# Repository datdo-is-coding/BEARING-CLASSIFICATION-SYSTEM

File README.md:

# 🏭 HỆ THỐNG KIỂM TRA & PHÂN LOẠI VÒNG BI TỰ ĐỘNG
## (AUTOMATED BEARING CLASSIFICATION SYSTEM)

Hệ thống tự động hóa công nghiệp kiểm tra và phân loại khuyết tật vòng bi kết hợp **Kiến trúc phân tán Edge - Cloud/Web**:
- **Trạm Điều Khiển Tại Chỗ (Edge Station - C# WinForms)**: Giao tiếp trực tiếp với phần cứng mạch điều khiển ESP32, thu nhận Camera DirectShow, chạy suy luận AI cục bộ 2 tầng (**YOLOv8 + ResNet-34 qua ONNX Runtime**) và điều khiển cánh tay Robot 4 bậc tự do (**4-DOF Arm**).
- **Hệ Thống Web Quản Lý & Giám Sát IoT (Central Web Dashboard - Python Flask)**: Kết nối với App C# qua **Mạng LAN nội bộ hoặc Internet (TCP/IP)**, cung cấp giao diện Web trực quan theo dõi thời gian thực, quản lý thống kê sản lượng OK/NG, lưu trữ lịch sử SQLite và điều khiển từ xa.
- **Phần Cứng & Cơ Điện Tử (Embedded & Mechatronics)**: Vi điều khiển **ESP32**, băng tải cấp phôi cảm biến quang NPN, mạch công suất cách ly và đầu gắp **nam châm điện (Electromagnet)**.

---

## 📑 Bảng Mục Lục
1. [Kiến Trúc Tổng Thể Hệ Thống](#-1-kiến-trúc-tổng-thể-hệ-thống)
2. [Quy Trình Hoạt Động (End-to-End Workflow)](#-2-quy-trình-hoạt-động-end-to-end-workflow)
3. [Chi Tiết Các Phân Hệ Công Nghệ](#-3-chi-tiết-các-phân-hệ-công-nghệ)
   - [3.1. Trạm điều khiển C# WinForms (Edge Control App)](#31-trạm-điều-khiển-c-winforms-edge-control-app)
   - [3.2. Web Quản Lý & Giám Sát IoT (Flask Dashboard Server)](#32-web-quản-lý--giám-sát-iot-flask-dashboard-server)
   - [3.3. Pipeline AI 2 tầng: YOLOv8n + ResNet-34 (ONNX Runtime)](#33-pipeline-ai-2-tầng-yolov8n--resnet-34-onnx-runtime)
   - [3.4. Vi điều khiển nhúng ESP32 & Động học Robot (Firmware)](#34-vi-điều-khiển-nhúng-esp32--động-học-robot-firmware)
   - [3.5. Phần cứng, Mạch PCB & Cơ khí (Hardware & Mechanics)](#35-phần-cứng-mạch-pcb--cơ-khí-hardware--mechanics)
4. [Giao Thức Truyền Thông & Kết Nối Đa Tầng](#-4-giao-thức-truyền-thông--kết-nối-đa-tầng)
   - [4.1. Giao tiếp LAN / TCP/IP (App C# $\leftrightarrow$ Web Quản lý)](#41-giao-tiếp-lan--tcpip-app-c--web-quản-lý)
   - [4.2. Giao tiếp Serial UART (App C# $\leftrightarrow$ Bo mạch ESP32)](#42-giao-tiếp-serial-uart-app-c--bo-mạch-esp32)
5. [Cấu Trúc Thư Mục Dự Án](#-5-cấu-trúc-thư-mục-dự-án)
6. [Hướng Dẫn Cài Đặt & Vận Hành](#-6-hướng-dẫn-cài-đặt--vận-hành)
7. [Kết Quả Đạt Được](#-7-kết-quả-đạt-được)

---

## 🏛️ 1. Kiến Trúc Tổng Thể Hệ Thống

Hệ thống được thiết kế theo mô hình phân tầng công nghiệp hiện đại (**Edge Controller $\leftrightarrow$ IoT Web Server**):

```
┌────────────────────────────────────────────────────────────────────────────────────────┐
│                   HỆ THỐNG GIÁM SÁT & QUẢN LÝ TRUNG TÂM (WEB IOT DASHBOARD)             │
│                                                                                        │
│   • Nền tảng: Python Flask / HTML5 / CSS3 / JavaScript / SQLite                        │
│   • Truy cập đa thiết bị: Trình duyệt PC, Tablet, Smartphone qua LAN / Internet        │
│   • Chức năng: Thống kê sản lượng Realtime, Giám sát Camera Snapshot, Lịch sử DB,       │
│                Điều khiển bắt đầu/dừng, Chế độ Mô phỏng / Thực tế                      │
└───────────────────────────────────────────▲────────────────────────────────────────────┘
                                            │
                                            │ MẠNG LAN / INTERNET (TCP/IP - HTTP REST API)
                                            │ • POST /api/detection (Kết quả AI, độ tin cậy)
                                            │ • POST /api/heartbeat (Trạng thái Online/Offline)
                                            │ • GET /api/status     (Trạng thái điều khiển)
                                            │ • GET /snapshot.jpg   (Hình ảnh camera trạm)
                                            ▼
┌────────────────────────────────────────────────────────────────────────────────────────┐
│                   TRẠM ĐIỀU KHIỂN & SUY LUẬN TẠI CHỖ (APP C# WINFORMS)                  │
│                                                                                        │
│   ┌────────────────────────────────────────┐  ┌─────────────────────────────────────┐  │
│   │        GIAO DIỆN WINFORMS (.NET 8)     │  │        ONNX RUNTIME AI PIPELINE     │  │
│   │  • Video Stream trực tiếp (OpenCV)     │  │  • Stage 1: yolo_bearing.onnx       │  │
│   │  • Mô phỏng Robot 3D (WPF/SharpDX)     │  │    (Định vị Bounding Box & Tâm)     │  │
│   │  • Quản lý cổng COM & cấu hình mạng    │  │  • Stage 2: resnet34_bearing.onnx   │  │
│   │  • Đồng bộ dữ liệu sang Web Dashboard  │  │    (Phân loại 4 lớp khuyết tật)     │  │
│   └────────────────────────────────────────┘  └─────────────────────────────────────┘  │
└───────────────────▲────────────────────────────────────────────▲───────────────────────┘
                    │                                            │
  (Camera Feed USB) │                                            │ Giao tiếp Serial UART
  DirectShow/OpenCV │                                            │ (Baud 9600/115200)
                    │                                            ▼
┌───────────────────┴───────┐                 ┌──────────────────────────────────────────┐
│  CAMERA QUAN SÁT TẠI TRẠM │                 │  BO MẠCH ĐIỀU KHIỂN TRUNG TÂM (ESP32)   │
│  • Độ phân giải cao       │                 │  • Thu nhận tín hiệu Cảm biến quang 24V  │
│  • Tiêu cự chuẩn buồng soi│                 │  • Giải thuật Động học nghịch (4-DOF IK) │
└───────────────────────────┘                 │  • Giao tiếp I2C điều khiển PCA9685      │
                                              │  • Đóng cắt MOSFET Băng tải & Nam châm   │
                                              └────────────────────┬─────────────────────┘
                                                                   │ (PWM 50Hz & Công suất)
                                                                   ▼
                                              ┌──────────────────────────────────────────┐
                                              │      CƠ CẤU CHẤP HÀNH NGOẠI VI           │
                                              │  • Động cơ Servo MG996R (Joint 1, 2, 3)  │
                                              │  • Micro Servo SG90 (Joint 4 Wrist)      │
                                              │  • Nam châm điện từ tính gắp phôi        │
                                              │  • Động cơ DC kéo Băng tải cấp phôi      │
                                              │  • Cảm biến quang phát hiện vị trí phôi  │
                                              └──────────────────────────────────────────┘
```

---

## 🔄 2. Quy Trình Hoạt Động (End-to-End Workflow)

```mermaid
flowchart TD
    A([Khởi động hệ thống]) --> B[App C# kết nối ESP32 qua Serial & Camera USB]
    B --> C[App C# kết nối Web Dashboard qua LAN/TCP-IP]
    C --> D[Web Dashboard phát lệnh BẮT ĐẦU CHU TRÌNH]
    D --> E[App C# kích hoạt Băng tải chạy cấp vòng bi]
    E --> F{Cảm biến quang phát hiện phôi?}
    F -- Chưa tới --> E
    F -- Đã phát hiện --> G[ESP32 báo ngắt -> App C# dừng Băng tải]
    G --> H[Camera chụp khung hình tĩnh trạm soi]
    H --> I[AI Stage 1: YOLOv8n phát hiện & crop vùng vòng bi ROI]
    I --> J[AI Stage 2: ResNet-34 phân loại 4 lớp khuyết tật]
    J --> K{Kết quả đánh giá?}
    K -- Normal --> L[Xác định: ĐẠT CHUẨN - OK]
    K -- Rusted / Damaged / Scratched --> M[Xác định: LỖI - NG]
    L --> N[App C# gửi HTTP POST /api/detection sang Web Dashboard]
    M --> N
    N --> O[Web cập nhật số lượng OK/NG & hiển thị nhật ký]
    L --> P[App C# tính toán tọa độ Cartesian chuyển lệnh UART sang ESP32]
    M --> P
    P --> Q[ESP32 giải IK -> Điều khiển Robot di chuyển đến tọa độ phôi]
    Q --> R[Bật Nam châm điện: Hút giữ vòng bi]
    R --> S[Robot nhấc phôi, quay thả vào khay tương ứng OK hoặc NG]
    S --> T[Ngắt Nam châm điện -> Robot trở về vị trí HOME]
    T --> U[ESP32 gửi tín hiệu hoàn thành chu trình về App C#]
    U --> V{Tiếp tục chu trình?}
    V -- Có --> E
    V -- Dừng --> W([Kết thúc vận hành])
```

---

## 🛠️ 3. Chi Tiết Các Phân Hệ Công Nghệ

### 3.1. Trạm Điều Khiển C# WinForms (Edge Control App)
*Thư mục mã nguồn: `software/DashBoardBearing/`*
- **Nền tảng**: `.NET 8.0 Windows Forms` kết hợp `WPF Interop` (`ElementHost`).
- **Giao tiếp phần cứng**:
  - Giao tiếp nối tiếp **Serial UART** (`System.IO.Ports`) đa luồng với ESP32: tự động kết nối lại khi mất tín hiệu, xử lý tập lệnh không đồng bộ không gây khóa giao diện.
  - Thu nhận hình ảnh trực tiếp qua `OpenCvSharp4` và `AForge.Video.DirectShow`.
- **Mô phỏng 3D thời gian thực**: Sử dụng `HelixToolkit.Wpf` và `SharpDX` mô phỏng trực quan chuyển động 4 khớp của Robot theo phản hồi thực tế từ ESP32.
- **Client LAN TCP/IP**:
  - Đóng vai trò Client gửi dữ liệu giám sát (`HttpClient`) lên Web Dashboard.
  - Cung cấp HTTP Endpoint nội bộ để Web Dashboard có thể đọc ảnh snapshot camera hiện tại.

### 3.2. Web Quản Lý & Giám Sát IoT (Flask Dashboard Server)
*Thư mục mã nguồn: `software/RobotBearingDashboard/`*
- **Nền tảng**: Python 3.10+, Flask, SQLite (`bearing.db`), HTML5/CSS3/JavaScript.
- **Tính năng trọng tâm**:
  - **Giám sát trực quan**: Hiển thị ảnh chụp trực tiếp từ trạm kiểm tra, nhãn phân loại, độ tin cậy và trạng thái chu trình.
  - **Thống kê sản lượng thời gian thực**: Biểu đồ trực quan và bộ đếm tổng sản phẩm, số lượng Đạt chuẩn (OK), các nhóm lỗi (Rỉ sét, Hư nắp, Khuyết tật bề mặt).
  - **Trạng thái phần cứng (Heartbeat)**: Giám sát tình trạng Online/Offline của module AI, Camera và mạch ESP32.
  - **Điều khiển từ xa**: Cho phép người quản trị ra lệnh Bắt đầu (`start`), Tạm dừng (`stop`), Đặt lại dữ liệu (`reset`) và chọn chế độ `real` (thực tế) hoặc `simulation` (mô phỏng).
  - **Lưu trữ & Xuất dữ liệu**: Tự động lưu nhật ký chi tiết vào SQLite và hỗ trợ trích xuất lịch sử phân loại.

### 3.3. Pipeline AI 2 Tầng: YOLOv8n + ResNet-34 (ONNX Runtime)
Hệ thống sử dụng cơ chế xử lý phân tầng nhằm tối ưu đồng thời tốc độ và độ chính xác:

| Tiêu chí | Giai đoạn 1 (Stage 1 - Detection) | Giai đoạn 2 (Stage 2 - Classification) |
| :--- | :--- | :--- |
| **Mô hình** | **YOLOv8n (Nano)** | **ResNet-34 (Deep Residual Net)** |
| **Vai trò** | Định vị Bounding Box & tọa độ tâm phôi $(X_c, Y_c)$ | Phân tích cấu trúc vi khuyết tật bề mặt |
| **Kích thước đầu vào** | $640 \times 640 \times 3$ | $224 \times 224 \times 3$ (Vùng ROI cắt từ BBox) |
| **Số lượng nhãn** | 1 lớp: `bearing` | 4 lớp: `normal`, `damaged_shield`, `rusted`, `surface_damage` |
| **Độ chính xác** | **Precision**: 98.9% \| **mAP@50**: **99.46%** | **Độ chính xác tổng**: **97.45%** \| **Macro F1**: **97.18%** |
| **Thời gian thực thi** | ~15 – 25 ms | ~8 – 15 ms |
| **Triển khai tại App C#** | `Microsoft.ML.OnnxRuntime` (`yolo_bearing.onnx`) | `Microsoft.ML.OnnxRuntime` (`resnet34_bearing.onnx`) |

#### Chi tiết độ chính xác phân loại 4 lớp (Tập Test độc lập 235 mẫu):
- `normal` (Đạt chuẩn $\rightarrow$ **OK**): Precision **97.7%**, Recall **91.3%**, F1 **94.4%**.
- `damaged_shield` (Hư nắp chắn bụi $\rightarrow$ **NG**): Precision **97.7%**, Recall **100.0%**, F1 **98.8%**.
- `rusted` (Gỉ sét oxy hóa $\rightarrow$ **NG**): Precision **97.3%**, Recall **99.1%**, F1 **98.2%**.
- `surface_damage` (Trầy xước/khuyết tật mặt lăn $\rightarrow$ **NG**): Precision **97.3%**, Recall **97.3%**, F1 **97.3%**.

### 3.4. Vi Điều Khiển Nhúng ESP32 & Động Học Robot (Firmware)
*Thư mục mã nguồn: `firmware/`*
- **Vi điều khiển**: ESP32-WROOM-32D (2 nhân Xtensa 240MHz).
- **Môi trường phát triển**: PlatformIO Core / C++ Framework Arduino.
- **Động học nghịch (Inverse Kinematics - IK)**:
  - Giải phương trình động học giải tích xác định góc 4 khớp $\theta_1, \theta_2, \theta_3, \theta_4$ từ tọa độ đích $(X, Y, Z)$ gửi từ App C#.
  - Kiểm tra điều kiện biên không gian làm việc (`OUT OF WORKSPACE`) và tránh điểm kỳ dị (`SINGULARITY`).
- **Máy trạng thái điều khiển (FSM)**: `IDLE`, `WAIT_SENSOR`, `MOVE_PICK`, `MAG_ON`, `MOVE_PLACE`, `MAG_OFF`, `HOME`, `ERROR`.
- **Giao tiếp phần cứng ngoại vi**:
  - Giao tiếp I2C Master tới IC tạo xung PWM PCA9685 (tần số 50Hz, phân giải 12-bit).
  - Đọc tín hiệu ngắt từ cảm biến quang qua bộ cách ly quang Opto PC817.
  - Điều khiển tầng kích MOSFET đóng ngắt động cơ băng tải và cuộn hút nam châm điện.

### 3.5. Phần Cứng, Mạch PCB & Cơ Khí (Hardware & Mechanics)
*Thư mục thiết kế: `hardware/`*
- **Cơ cấu tay máy 4-DOF**:
  - Thiết kế 3D bằng SolidWorks (`SLDASM`, `STEP`).
  - Khớp 1 (Đế), Khớp 2 (Vai), Khớp 3 (Khuỷu): Sử dụng Servo kim loại lực kéo cao **MG996R**.
  - Khớp 4 (Cổ tay xoay đầu gắp): Sử dụng Micro Servo **SG90**.
  - Đầu gắp: Sử dụng **Nam châm điện (Electromagnet)** hút giữ bề mặt vòng bi chắc chắn, tích hợp mạch dập xung ngược Flyback Diode.
- **Mạch điện tử điều khiển (PCB Hardware)**:
  - Thiết kế hoàn chỉnh trên **KiCad EDA** (`robot4dof.kicad_sch`, `robot4dof.kicad_pcb`).
  - Khối nguồn hạ áp cách ly: XL4015 (5A) cấp riêng cho hệ thống Servo, XL1509 và AMS1117 cấp cho mạch logic ESP32 nhằm triệt tiêu nhiễu sụt áp khi khởi động động cơ.
- **Băng tải & Cảm biến**:
  - Băng tải đai cao su nguồn 24V tốc độ ổn định.
  - Cảm biến thu phát quang học NPN 24V định vị phôi dừng chính xác tại buồng chụp.

---

## 📡 4. Giao Thức Truyền Thông & Kết Nối Đa Tầng

```
┌────────────────────┐            Mạng LAN / TCP-IP (HTTP REST)            ┌──────────────────────┐
│  Web Quản Lý IoT   │ ◄─────────────────────────────────────────────────► │    App C# WinForms   │
│  (Flask Dashboard) │   POST /api/detection, POST /api/heartbeat,...      │    (Edge Control)    │
└────────────────────┘                                                     └──────────┬───────────┘
                                                                                      │
                                                                   Cáp Serial (UART)  │ Cổng COM Nối Tiếp
                                                                   Baud 9600 / 115200 │ 8-N-1
                                                                                      ▼
                                                                           ┌──────────────────────┐
                                                                           │  Bo Mạch Điều Khiển  │
                                                                           │       (ESP32)        │
                                                                           └──────────────────────┘
```

### 4.1. Giao Tiếp LAN / TCP/IP (App C# $\leftrightarrow$ Web Quản Lý)

Kết nối thông qua giao thức HTTP REST API qua mạng LAN nội bộ (hoặc Internet TCP/IP):

| Endpoint | Phương thức | Bên gửi | Dữ liệu truyền (Payload JSON) | Chức năng |
| :--- | :---: | :---: | :--- | :--- |
| `/api/detection` | `POST` | App C# $\rightarrow$ Web | `{"category": "OK", "confidence": 0.975, "source": "ai", "cycle_id": 102}` | Gửi kết quả phân loại vòng bi |
| `/api/heartbeat` | `POST` | App C# $\rightarrow$ Web | `{"ai_online": true, "camera_online": true, "esp_online": true}` | Cập nhật trạng thái phần cứng |
| `/api/status` | `GET` | Web $\leftrightarrow$ App C# | Trả về JSON trạng thái hệ thống, chế độ chạy và số lượng | Đồng bộ trạng thái giao diện |
| `/api/control` | `POST` | Web $\rightarrow$ App C# | `{"action": "start"}` (hoặc `"stop"`, `"reset"`, `"real"`, `"demo"`) | Gửi lệnh điều khiển từ xa |
| `/snapshot.jpg` | `GET` | Web $\rightarrow$ App C# | Trả về luồng ảnh JPEG khung hình hiện tại của camera | Hiển thị hình ảnh trạm soi trên Web |

### 4.2. Giao Tiếp Serial UART (App C# $\leftrightarrow$ Bo Mạch ESP32)
- **Thông số truyền**: Baudrate: `9600 bps` (hoặc `115200 bps`), Data Bits: `8`, Parity: `None`, Stop Bits: `1`, Ký tự ngắt dòng: `\n`.

#### Bảng Lệnh Từ App C# $\rightarrow$ ESP32:
| Cú pháp lệnh | Ý nghĩa | Mô tả |
| :--- | :--- | :--- |
| `START` | Bắt đầu chu trình nạp lệnh | Khởi động hàng đợi chuyển động |
| `MOV <x> <y> <z>` | Di chuyển đầu gắp đến tọa độ | Tọa độ điểm gắp hoặc điểm thả phôi (mm) |
| `MAG <1\|0>` | Đóng/Ngắt nam châm điện | `MAG 1`: Hút giữ phôi \| `MAG 0`: Thả phôi |
| `HOME` | Về vị trí chờ an toàn | Đưa 4 khớp về góc an toàn mặc định |
| `CONV <1\|0>` | Đóng/Ngắt băng tải | Điều khiển động cơ băng tải chạy/dừng |
| `STOP` | Dừng khẩn cấp | Dừng toàn bộ chuyển động ngay lập tức |

#### Bản Tin Phản Hồi Từ ESP32 $\rightarrow$ App C#:
| Bản tin phản hồi | Ý nghĩa |
| :--- | :--- |
| `SENSOR_TRIGGERED` | Tín hiệu cảm biến quang ngắt báo phôi đã đến trạm dừng |
| `A <J1> <J2> <J3> <J4>` | Góc quay hiện tại của 4 khớp servo (chu kỳ 50ms để render 3D) |
| `CYCLE_DONE <id>` | Báo hoàn thành chu trình gắp thả thành công |
| `IK ERROR: OUT OF WORKSPACE` | Cảnh báo tọa độ phôi nằm ngoài bán kính vươn tới của robot |

---

## 📂 5. Cấu Trúc Thư Mục Dự Án

```
BEARING-CLASSIFICATION-SYSTEM/
│
├── firmware/                              # Firmware nhúng điều khiển ESP32
│   ├── platformio.ini                     # Cấu hình PlatformIO & thư viện phụ thuộc
│   ├── include/                           # Thư viện header C++ (.hpp)
│   │   ├── CLI.hpp                        # Bộ thông dịch lệnh Serial UART
│   │   ├── control.hpp                    # Cấu hình I2C PCA9685 & xung servo
│   │   └── kinematics.hpp                 # Giải thuật Động học nghịch (IK 4-DOF)
│   └── src/                               # Mã nguồn C++ triển khai
│       ├── main.cpp                       # Điểm khởi chạy, hàm setup() & loop()
│       ├── CLI.cpp                        # Xử lý chuỗi lệnh nhận từ App C#
│       ├── control.cpp                    # Điều khiển PWM, MOSFET băng tải & nam châm
│       └── kinematics.cpp                 # Thuật toán tính góc các khớp
│
├── hardware/                              # Thiết kế cơ khí CAD và mạch điện tử PCB
│   ├── cad/                               # File mô hình 3D SolidWorks (.SLDASM, .STEP)
│   │   ├── Assem1.SLDASM                  # Lắp ráp tổng thể cánh tay Robot 4-DOF
│   │   ├── base.SLDPRT                    # Chi tiết bệ đỡ xoay
│   │   ├── arm bar.SLDPRT                 # Cụm cánh tay chịu lực
│   │   ├── magnet.SLDPRT                  # Gá giữ nam châm điện
│   │   └── mg996R_v2.step                 # Mô hình 3D chuẩn servo MG996R
│   └── pcb/                               # Thiết kế bo mạch KiCad EDA
│       ├── robot4dof.kicad_sch            # Sơ đồ nguyên lý mạch điều khiển
│       ├── robot4dof.kicad_pcb            # Bản vẽ layout bo mạch in
│       └── robot4dof_gerber/              # Tệp Gerber phục vụ gia công sản xuất
│
├── software/                              # Toàn bộ phần mềm hệ thống máy tính
│   │
│   ├── DashBoardBearing/                  # [EDGE] Ứng dụng điều khiển trung tâm C# WinForms
│   │   ├── DashBoardBearing.sln           # Visual Studio Solution (.NET 8.0)
│   │   ├── DashBoardBearing.csproj        # Cấu hình dependencies & NuGet Packages
│   │   ├── CameraManager.cs               # Bắt hình camera, OpenCV & gọi ONNX Runtime
│   │   ├── SerialManager.cs               # Giao tiếp nối tiếp COM/UART với ESP32
│   │   ├── RoundedPanel.cs                # Component giao diện phẳng hiện đại
│   │   ├── FormHome.cs                    # Màn hình camera live, nhận diện & gửi dữ liệu Web
│   │   ├── FormRobot.cs                   # Màn hình tích hợp mô phỏng Robot 3D (WPF/SharpDX)
│   │   ├── FormSetting.cs                 # Cấu hình cổng COM, Camera và IP Web Dashboard
│   │   ├── FormLog.cs                     # Ghi nhật ký vận hành tại chỗ
│   │   └── Model/                         # Trọng số mô hình AI xuất chuẩn ONNX
│   │       ├── yolo_bearing.onnx          # Model Stage 1: Phát hiện BBox vòng bi
│   │       └── resnet34_bearing.onnx      # Model Stage 2: Phân loại 4 lớp khuyết tật
│   │
│   └── RobotBearingDashboard/             # [WEB IOT] Ứng dụng Web Quản Lý & Giám Sát
│       └── RobotBearingDashboard/
│           ├── app.py                     # Máy chủ backend Python Flask & REST API
│           ├── requirements.txt           # Thư viện Flask, requests
│           ├── bearing.db                 # Cơ sở dữ liệu SQLite lưu trữ lịch sử
│           ├── templates/
│           │   └── index.html             # Giao diện Web Dashboard thời gian thực
│           ├── static/                    # CSS, JS, hình ảnh giao diện Web
│           ├── send_ai_example.py         # Script Python mẫu gửi dữ liệu test API
│           └── README.md                  # Hướng dẫn chi tiết phân hệ Web Dashboard
│
├── training/                              # Mã nguồn huấn luyện & nghiên cứu AI (PyTorch)
│   ├── configs/config.yaml                # Siêu tham số huấn luyện
│   ├── models/class_mapping.json          # Bảng ánh xạ ID nhãn sang tên lỗi
│   ├── weights/                           # Checkpoint trọng số tối ưu (.pt, .pth)
│   ├── tools/                             # Tool cắt ROI, gán nhãn, tiền xử lý dữ liệu
│   ├── training/                          # Script huấn luyện YOLOv8 & Fine-tune ResNet-34
│   ├── main.py                            # Script chạy thực nghiệm độc lập trên Python
│   └── requirements.txt                   # Thư viện Python (torch, torchvision, ultralytics)
│
├── NCKH_REQUIREMENT.md                    # Bảng theo dõi các nội dung hoàn thiện báo cáo NCKH
└── README.md                              # Tài liệu hướng dẫn tổng thể dự án
```

---

## 🚀 6. Hướng Dẫn Cài Đặt & Vận Hành

### 6.1. Chuẩn Bị Môi Trường
1. **Phần cứng**: Máy tính chạy Windows 10/11, bo mạch ESP32, bộ đổi nguồn 24V (băng tải) và 5V-6V (servo), cáp nối USB-UART, camera trạm soi.
2. **Phần mềm phát triển**:
   - Visual Studio 2022 (cài gói **.NET Desktop Development**).
   - .NET 8.0 SDK.
   - Python 3.10 trở lên.
   - VS Code có cài extension **PlatformIO IDE**.

---

### 6.2. Nạp Firmware Cho Bo Mạch ESP32
1. Mở thư mục `firmware/` bằng VS Code.
2. Cắm cáp USB nối ESP32 vào máy tính.
3. Nhấn nút **PlatformIO: Upload** trên thanh trạng thái để biên dịch và nạp firmware.

---

### 6.3. Khởi Chạy Web Quản Lý (Flask Web Dashboard)
1. Mở terminal (PowerShell) và chuyển vào thư mục Web Dashboard:
   ```powershell
   cd software/RobotBearingDashboard/RobotBearingDashboard
   ```
2. Tạo môi trường ảo và cài đặt thư viện:
   ```powershell
   py -m venv .venv
   .\.venv\Scripts\Activate.ps1
   pip install -r requirements.txt
   ```
3. Khởi chạy Web Server:
   ```powershell
   python app.py
   ```
4. Truy cập giao diện trên trình duyệt web:
   ```
   http://127.0.0.1:5000
   ```
   *(Hoặc truy cập qua địa chỉ IP mạng LAN của máy chủ: `http://192.168.x.x:5000`)*.

---

### 6.4. Khởi Chạy Ứng Dụng C# WinForms (Edge Control Station)
1. Mở `software/DashBoardBearing/DashBoardBearing.sln` bằng Visual Studio 2022.
2. Đảm bảo cấu hình đường dẫn IP Web Dashboard trong phần cấu hình mạng (mặc định: `http://127.0.0.1:5000` hoặc IP LAN của máy chủ).
3. Kiểm tra các mô hình AI ONNX đã nằm đúng trong thư mục `software/DashBoardBearing/Model/`:
   - `yolo_bearing.onnx`
   - `resnet34_bearing.onnx`
4. Chọn cấu hình **Release \| x64** và nhấn **Start (F5)** để khởi chạy ứng dụng.

---

### 6.5. Vận Hành Đồng Bộ Toàn Hệ Thống
1. **Trên App C# WinForms**:
   - Vào tab **Setting**: Chọn cổng COM của ESP32 (ví dụ: `COM3`, baudrate `9600`), nhấn **Connect Serial**.
   - Chọn Camera soi phôi trong danh sách và nhấn **Start Camera**.
   - Bật kết nối đồng bộ dữ liệu tới **Web Dashboard**.
2. **Trên Web Dashboard**:
   - Kiểm tra nhịp tim phần cứng: biểu tượng **AI Online**, **Camera Online**, **ESP Online** chuyển sang màu xanh.
   - Chọn chế độ **Thực tế (Real Mode)** và nhấn **Bắt đầu (Start)**.
3. **Chu trình tự động**:
   - Băng tải chạy cấp vòng bi vào buồng soi.
   - Khi cảm biến quang ngắt, băng tải dừng lại.
   - Camera chụp ảnh, App C# suy luận AI 2 tầng (YOLOv8 + ResNet-34).
   - App C# tự động gửi bản tin phân loại qua mạng LAN sang Web Dashboard để ghi log và thống kê.
   - App C# truyền lệnh gắp tới ESP32; Robot gắp thả vòng bi vào đúng khay phân loại (Khay OK hoặc Khay NG).
   - Sau khi hoàn thành, robot trở về vị trí Home và băng tải tiếp tục chạy cấp sản phẩm mới.

---

## 🏆 7. Kết Quả Đạt Được

- ✅ **Kiến trúc hệ thống phân tán hoàn chỉnh**: Kết hợp linh hoạt giữa khả năng điều khiển cứng thời gian thực của C# WinForms và khả năng giám sát từ xa đa nền tảng qua mạng LAN của Web IoT Flask.
- ✅ **Độ tin cậy nhận diện cao**: Mô hình AI 2 tầng đạt độ chính xác **97.45%**, phân loại chuẩn xác 4 trạng thái vòng bi công nghiệp.
- ✅ **Vận hành an toàn & đồng bộ**: Cơ chế khóa liên động giữa cảm biến quang, băng tải và máy trạng thái robot giúp loại bỏ nguy cơ va chạm cơ khí và lỗi kẹt phôi.
- ✅ **Khả năng mở rộng công nghiệp**: Dễ dàng tích hợp thêm các trạm kiểm tra mới vào cùng một Web Dashboard quản lý thông qua giao thức mạng TCP/IP tiêu chuẩn.

---
*Dự án thuộc Đề tài Nghiên cứu Khoa học Sinh viên - Khoa Tự động hoá, Trí tuệ nhân tạo và Hệ thống thông minh, Trường Đại học Điện lực.*

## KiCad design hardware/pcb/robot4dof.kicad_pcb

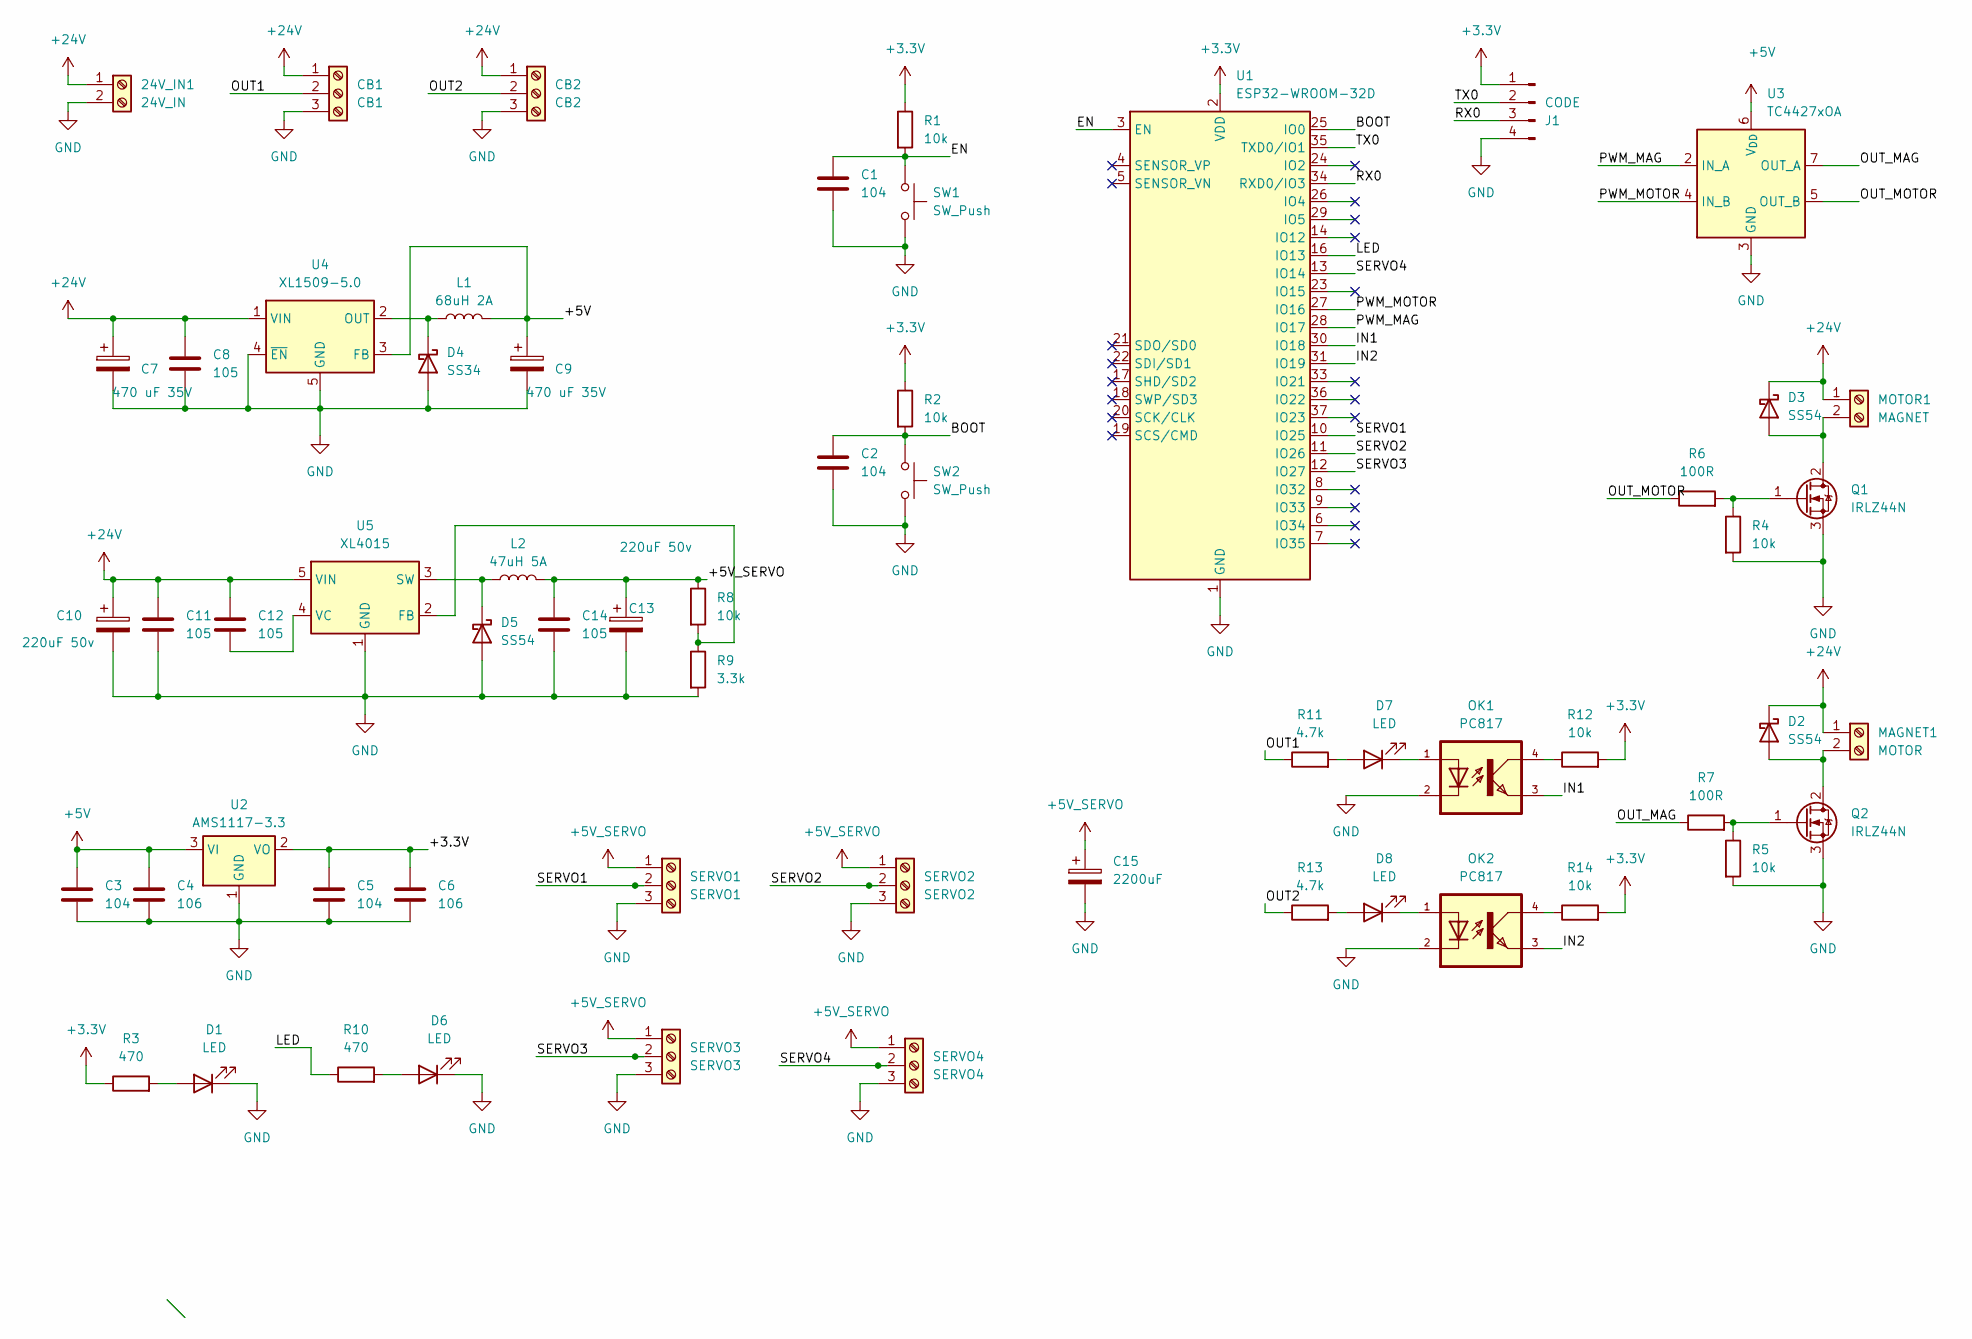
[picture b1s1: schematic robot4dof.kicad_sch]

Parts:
24V_IN1: 24V_IN; TerminalBlock_TE_282834-2_1x02_P2.54mm_Horizontal
C1, C2, C3, C5: 104; C_0805_2012Metric_Pad1.18x1.45mm_HandSolder
C4, C6: 106; C_0805_2012Metric_Pad1.18x1.45mm_HandSolder
C7, C9: 470 uF 35V; CP_Elec_8x10.5
C8, C11, C12, C14: 105; C_0805_2012Metric_Pad1.18x1.45mm_HandSolder
C10, C13: 220uF 50v; CP_Elec_8x10.5
C15: 2200uF; C_Radial_D10.0mm_H20.0mm_P5.00mm
CB1: CB1; TerminalBlock_TE_282834-3_1x03_P2.54mm_Horizontal
CB2: CB2; TerminalBlock_TE_282834-3_1x03_P2.54mm_Horizontal
D1, D6, D7, D8: LED; LED_0805_2012Metric_Pad1.15x1.40mm_HandSolder
D2, D3, D5: SS54; D_SMA_Handsoldering
D4: SS34; D_SMA_Handsoldering
J1: CODE; PinHeader_1x04_P2.54mm_Vertical
L1: 68uH 2A; L_7.3x7.3_H3.5
L2: 47uH 5A; L_Toroid_Vertical_L21.6mm_W9.1mm_P8.40mm_Bourns_5700
MAGNET1: MOTOR; TerminalBlock_TE_282834-2_1x02_P2.54mm_Horizontal
MOTOR1: MAGNET; TerminalBlock_TE_282834-2_1x02_P2.54mm_Horizontal
OK1, OK2: PC817; DIL04; MPN PC817X4J000F
Q1, Q2: IRLZ44N; TO-220-3_Vertical
R1, R2, R4, R5, R8, R12, R14: 10k; R_0805_2012Metric_Pad1.20x1.40mm_HandSolder
R3, R10: 470; R_0805_2012Metric_Pad1.20x1.40mm_HandSolder
R6, R7: 100R; R_0805_2012Metric_Pad1.20x1.40mm_HandSolder
R9: 3.3k; R_0805_2012Metric_Pad1.20x1.40mm_HandSolder
R11, R13: 4.7k; R_0805_2012Metric_Pad1.20x1.40mm_HandSolder
SERVO1: SERVO1; TerminalBlock_TE_282834-3_1x03_P2.54mm_Horizontal
SERVO2: SERVO2; TerminalBlock_TE_282834-3_1x03_P2.54mm_Horizontal
SERVO3: SERVO3; TerminalBlock_TE_282834-3_1x03_P2.54mm_Horizontal
SERVO4: SERVO4; TerminalBlock_TE_282834-3_1x03_P2.54mm_Horizontal
SW1, SW2: SW_Push; SW_Tactile_SPST_NO_Straight_CK_PTS636Sx25SMTRLFS
U1: ESP32-WROOM-32D
U2: AMS1117-3.3; SOT-223-3_TabPin2
U3: TC4427xOA; SOIC-8_3.9x4.9mm_P1.27mm
U4: XL1509-5.0; SOIC-8_3.9x4.9mm_P1.27mm
U5: XL4015; TO-263-5_TabPin3

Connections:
+3.3V: C5.1, C6.1, J1.1, R1.1, R2.1, R3.1, R12.2, R14.2, U1.2 (VDD), U2.2 (VO)
+5V: C3.1, C4.1, C9.1, L1.2, U2.3 (VI), U3.6 (V_{DD}), U4.3 (FB)
+5V_SERVO: C13.1, C14.1, C15.1, L2.2, R8.1, SERVO1.1, SERVO2.1, SERVO3.1, SERVO4.1
+24V: 24V_IN1.1, C7.1, C8.1, C10.1, C11.1, C12.1, CB1.1, CB2.1, D2.1 (K), D3.1 (K), MAGNET1.1, MOTOR1.1, U4.1 (VIN), U5.5 (VIN)
/BOOT: C2.1, R2.2, SW2.1, U1.25 (IO0)
/EN: C1.1, R1.2, SW1.1, U1.3 (EN)
/IN1: OK1.3, U1.30 (IO18)
/IN2: OK2.3, U1.31 (IO19)
/LED: R10.1, U1.16 (IO13)
/OUT1: CB1.2, R11.1
/OUT2: CB2.2, R13.1
/OUT_MAG: R7.1, U3.7 (OUT_A)
/OUT_MOTOR: R6.1, U3.5 (OUT_B)
/PWM_MAG: U1.28 (IO17), U3.2 (IN_A)
/PWM_MOTOR: U1.27 (IO16), U3.4 (IN_B)
/RX0: J1.3, U1.34 (RXD0/IO3)
/SERVO1: SERVO1.2, U1.10 (IO25)
/SERVO2: SERVO2.2, U1.11 (IO26)
/SERVO3: SERVO3.2, U1.12 (IO27)
/SERVO4: SERVO4.2, U1.13 (IO14)
/TX0: J1.2, U1.35 (TXD0/IO1)
GND: 24V_IN1.2, C1.2, C2.2, C3.2, C4.2, C5.2, C6.2, C7.2, C8.2, C9.2, C10.2, C11.2, C13.2, C14.2, C15.2, CB1.3, CB2.3, D1.1 (K), D4.2 (A), D5.2 (A), D6.1 (K), J1.4, OK1.2, OK2.2, Q1.3 (S), Q2.3 (S), R4.2, R5.2, R9.2, SERVO1.3, SERVO2.3, SERVO3.3, SERVO4.3, SW1.2, SW2.2, U1.1 (GND), U1.15 (GND), U1.38 (GND), U1.39 (GND), U2.1 (GND), U3.3 (GND), U4.4 (~EN), U4.5 (GND), U4.6 (GND), U4.7 (GND), U4.8 (GND), U5.1 (GND)
unnamed: D1.2 (A), R3.2
unnamed: D2.2 (A), MAGNET1.2, Q2.2 (D)
unnamed: D3.2 (A), MOTOR1.2, Q1.2 (D)
unnamed: D4.1 (K), L1.1, U4.2 (OUT)
unnamed: D5.1 (K), L2.1, U5.3 (SW)
unnamed: D6.2 (A), R10.2
unnamed: D7.2 (A), R11.2
unnamed: D7.1 (K), OK1.1
unnamed: D8.2 (A), R13.2
unnamed: D8.1 (K), OK2.1
unnamed: OK1.4, R12.1
unnamed: OK2.4, R14.1
unnamed: Q1.1 (G), R4.1, R6.2
unnamed: Q2.1 (G), R5.1, R7.2
unnamed: R8.2, R9.1, U5.2 (FB)
unnamed: C12.2, U5.4 (VC)

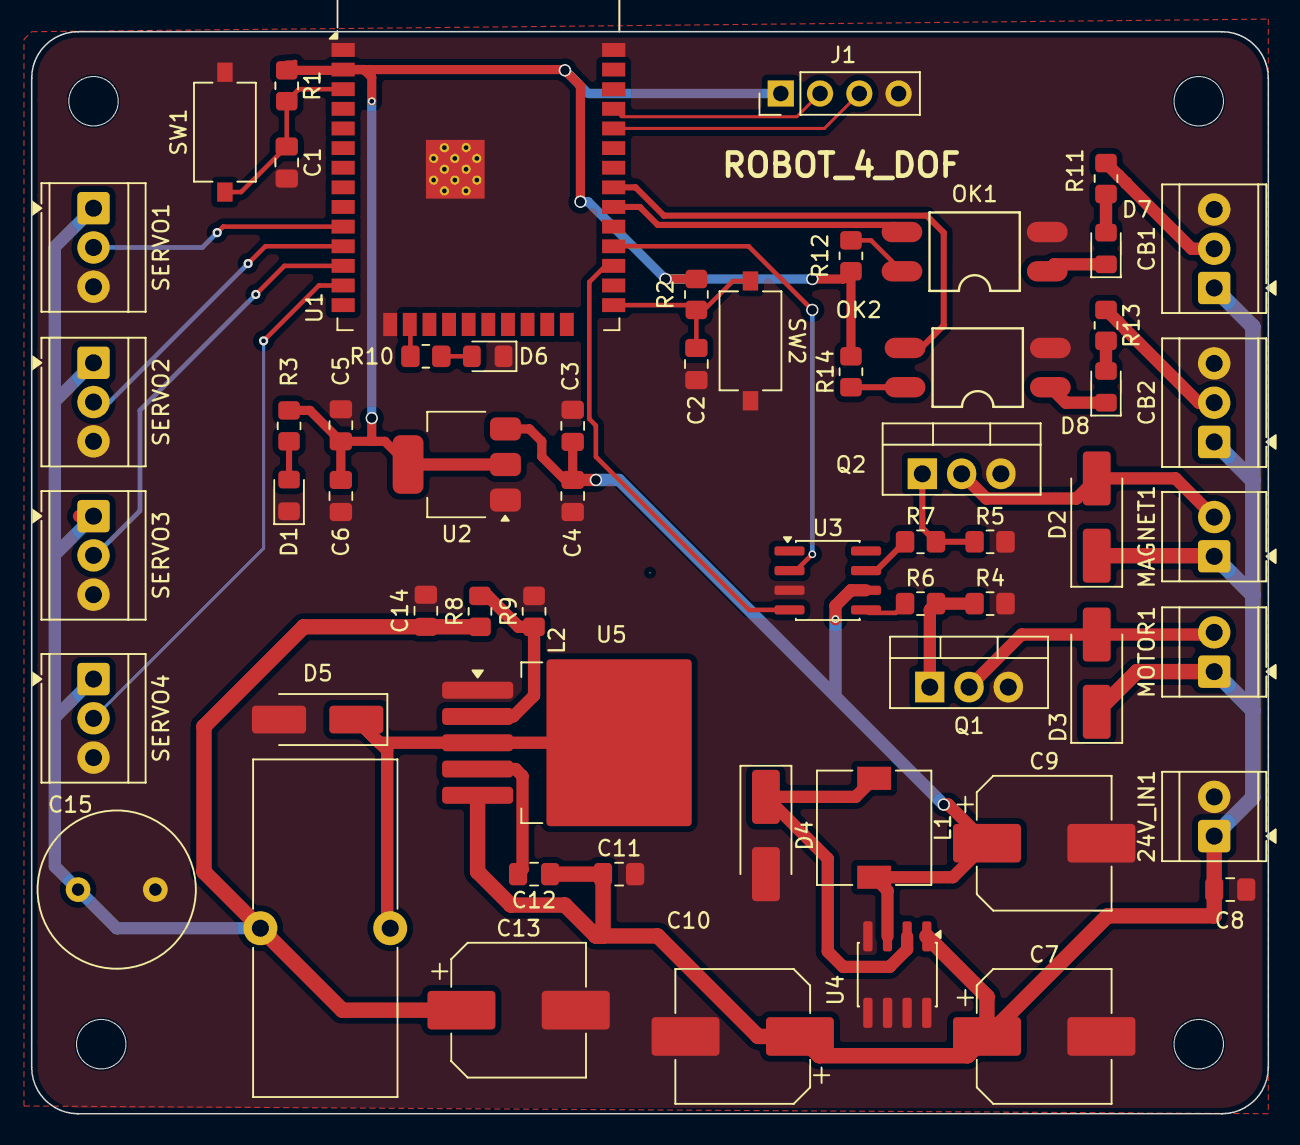
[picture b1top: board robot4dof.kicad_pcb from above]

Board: 2 copper layers, 80.0 x 70.0 mm, 60 parts (0 on the bottom side), 38 nets.

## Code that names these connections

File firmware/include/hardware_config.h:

#ifndef HARDWARE_CONFIG_H
#define HARDWARE_CONFIG_H

#include <Arduino.h>

// =============================================================================
// CẤU HÌNH CHÂN PHẦN CỨNG (HARDWARE PINOUT DEFINITION)
// Theo sơ đồ mạch nguyên lý PCB ESP32-WROOM-32D của hệ thống
// =============================================================================

// 1. ĐIỀU KHIỂN MOTOR BĂNG TẢI (PWM ĐIỀU TỐC)
#define PIN_MOTOR_PWM       16      // GPIO16 - Net PWM_MOTOR trên PCB
#define MOTOR_PWM_CHANNEL    0      // Kênh LEDC PWM của ESP32 (0-15)
#define MOTOR_PWM_FREQ    5000      // Tần số PWM 5kHz
#define MOTOR_PWM_RES        8      // Độ phân giải 8-bit (0 - 255)
#define MOTOR_DEFAULT_SPEED 180     // Tốc độ mặc định khi chạy băng tải

// 2. ĐIỀU KHIỂN NAM CHÂM ĐIỆN (ELECTROMAGNET)
#define PIN_MAGNET          17      // GPIO17 - Net PWM_MAG / OUT_MAG trên PCB
#define MAGNET_ON         HIGH      // Mức kích hoạt nam châm
#define MAGNET_OFF         LOW

// 3. CẢM BIẾN QUANG PHÁT HIỆN VẬT (OPTICAL SENSOR)
#define CB1                 18      // GPIO18 - Cảm biến quang 1 (IN1 trên PCB)
#define CB2                 19      // GPIO19 - Cảm biến quang 2 (IN2 trên PCB)
#define PIN_SENSOR_1        CB1
#define PIN_SENSOR_2        CB2

// Cảm biến được chọn ban đầu để kích hoạt dừng băng tải (Mặc định chọn CB1)
#define DEFAULT_ACTIVE_CB   CB1

// Trạng thái cảm biến:
// Bình thường (không có vòng bi): Chân ở mức HIGH
// Khi có vòng bi đi qua: Chân bị kéo xuống mức LOW (sườn âm HIGH -> LOW)
#define SENSOR_NORMAL_LEVEL HIGH
#define SENSOR_ACTIVE_LEVEL LOW     // Mức LOW = Phát hiện có vòng bi     

// 4. GIAO TIẾP PCA9685 CHO ROBOT 4-DOF
// GPIO25 = SDA, GPIO26 = SCL (được định nghĩa trong control.hpp)

#endif // HARDWARE_CONFIG_H
